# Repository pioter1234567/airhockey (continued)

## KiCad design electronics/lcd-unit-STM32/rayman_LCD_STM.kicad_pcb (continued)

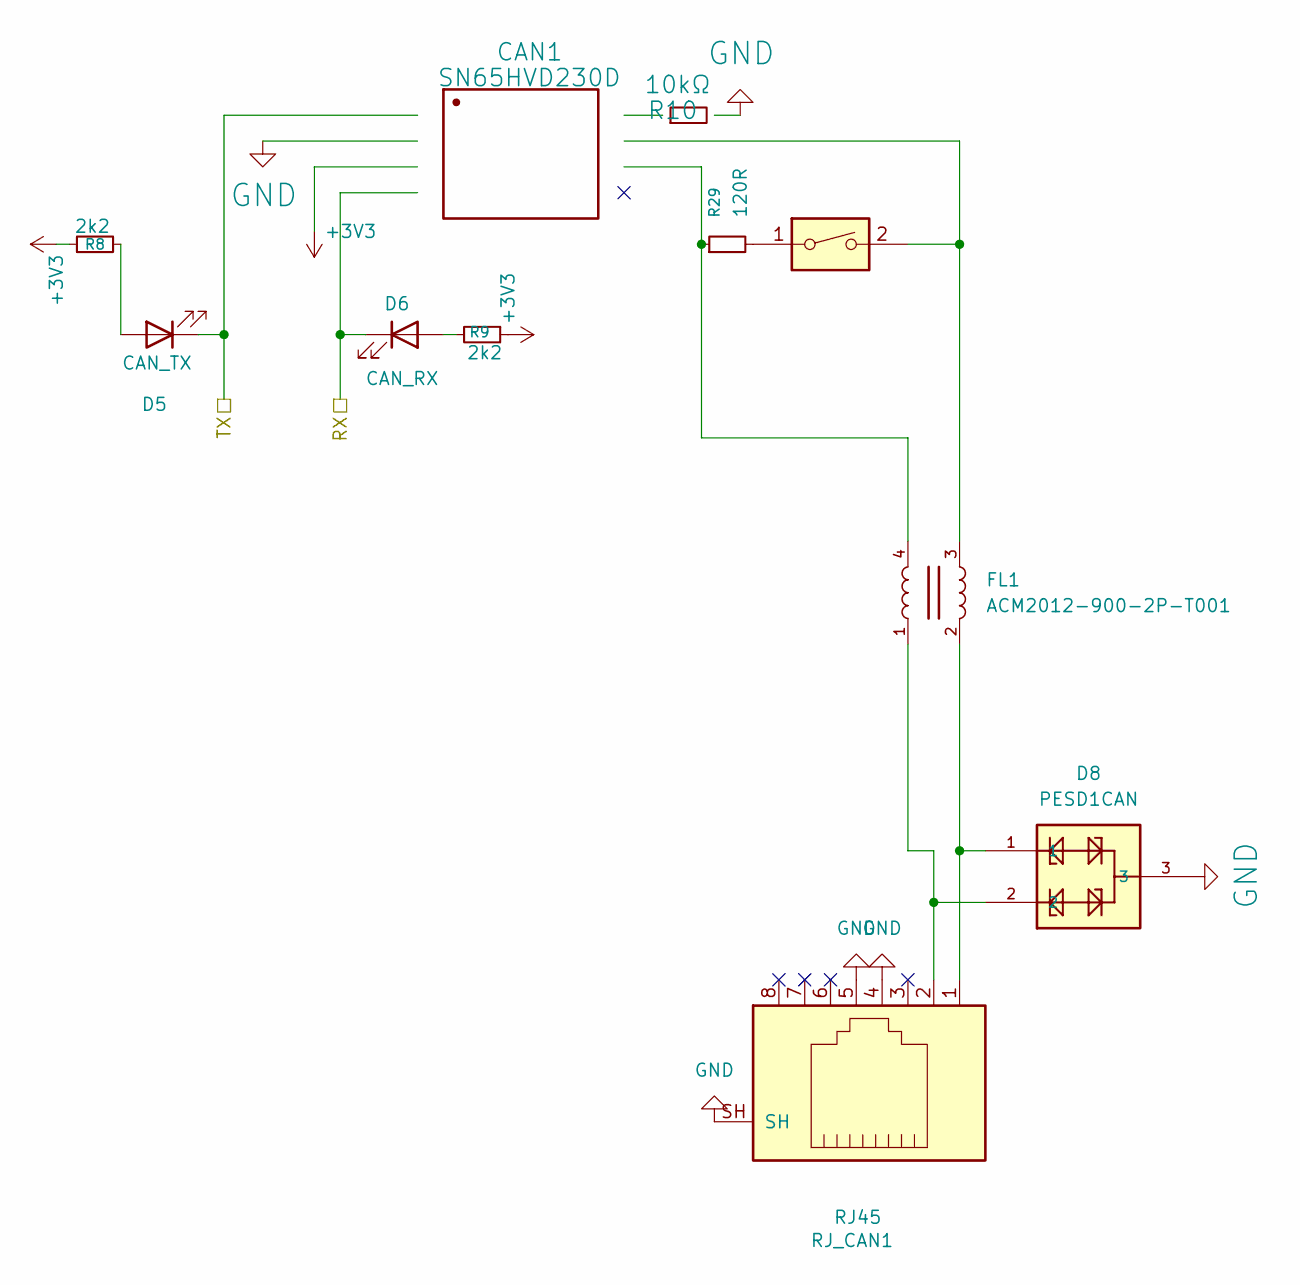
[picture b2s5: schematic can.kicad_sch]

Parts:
CAN1: SN65HVD230D; SOIC127P599X175-8N; Manufacturer Part SN65HVD230D
D5: CAN_TX; LED_0805_2012Metric
D6: CAN_RX; LED_0805_2012Metric
D8: PESD1CAN; SOT23-3
FL1: ACM2012-900-2P-T001; FIL_ACM2012-900-2P-T001
R8, R9: 2k2; R_0805_2012Metric
R10: 10kΩ; R_0805_2012Metric; Manufacturer Part RT0603LRA0710KL
R29: 120R; R_0805_2012Metric
RJ_CAN1: RJ45; RJ45_Amphenol_RJHSE5380
SW_CAN_T1: SW_DIP_x01; SW_DIP_SPSTx01_Slide_6.7x4.1mm_W7.62mm_P2.54mm_LowProfile

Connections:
+3V3: CAN1.3 (VCC), R8.1, R9.1; also elsewhere on the board
GND: CAN1.2 (GND), D8.3, R10.2, RJ_CAN1.4, RJ_CAN1.5, RJ_CAN1.SH; also elsewhere on the board
unnamed: CAN1.7 (CANH), FL1.3, SW_CAN_T1.2
unnamed: CAN1.6 (CANL), FL1.4, R29.1
unnamed: CAN1.8 (RS), R10.1
unnamed: D5.2 (A), R8.2
unnamed: D6.2 (A), R9.2
unnamed: D8.1, FL1.2, RJ_CAN1.1
unnamed: D8.2, FL1.1, RJ_CAN1.2
unnamed: R29.2, SW_CAN_T1.1
pa11: CAN1.4 (R), D6.1 (K); also elsewhere on the board
pa12: CAN1.1 (D), D5.1 (K); also elsewhere on the board

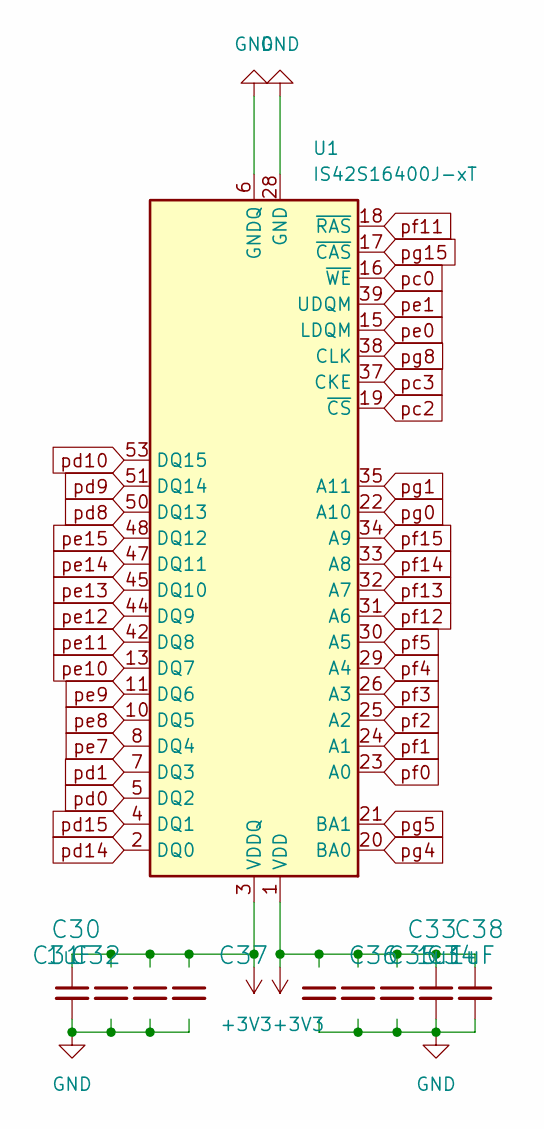
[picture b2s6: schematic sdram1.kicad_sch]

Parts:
C30, C33, C38: 1uF; C_0603_1608Metric; Manufacturer Part 0805ZD106KAT2A
C31, C32, C34, C35, C36, C37: 100nF; C_0603_1608Metric; Manufacturer Part 0805B104K160CT-C
U1: IS42S16400J-xT; TSOP-II-54_22.2x10.16mm_P0.8mm

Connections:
+3V3: C30.1, C31.1, C32.1, C33.1, C34.1, C35.1, C36.1, C37.1, C38.1, U1.1 (VDD), U1.3 (VDDQ), U1.9 (VDDQ), U1.14 (VDD), U1.27 (VDD), U1.43 (VDDQ), U1.49 (VDDQ); also elsewhere on the board
GND: C30.2, C31.2, C32.2, C33.2, C34.2, C35.2, C36.2, C37.2, C38.2, U1.6 (GNDQ), U1.12 (GNDQ), U1.28 (GND), U1.41 (GND), U1.46 (GNDQ), U1.52 (GNDQ), U1.54 (GND); also elsewhere on the board
pc0: U1.16 (~WE); also elsewhere on the board
pc2: U1.19 (~CS); also elsewhere on the board
pc3: U1.37 (CKE); also elsewhere on the board
pd0: U1.5 (DQ2); also elsewhere on the board
pd1: U1.7 (DQ3); also elsewhere on the board
pd8: U1.50 (DQ13); also elsewhere on the board
pd9: U1.51 (DQ14); also elsewhere on the board
pd10: U1.53 (DQ15); also elsewhere on the board
pd14: U1.2 (DQ0); also elsewhere on the board
pd15: U1.4 (DQ1); also elsewhere on the board
pe0: U1.15 (LDQM); also elsewhere on the board
pe1: U1.39 (UDQM); also elsewhere on the board
pe7: U1.8 (DQ4); also elsewhere on the board
pe8: U1.10 (DQ5); also elsewhere on the board
pe9: U1.11 (DQ6); also elsewhere on the board
pe10: U1.13 (DQ7); also elsewhere on the board
pe11: U1.42 (DQ8); also elsewhere on the board
pe12: U1.44 (DQ9); also elsewhere on the board
pe13: U1.45 (DQ10); also elsewhere on the board
pe14: U1.47 (DQ11); also elsewhere on the board
pe15: U1.48 (DQ12); also elsewhere on the board
pf0: U1.23 (A0); also elsewhere on the board
pf1: U1.24 (A1); also elsewhere on the board
pf2: U1.25 (A2); also elsewhere on the board
pf3: U1.26 (A3); also elsewhere on the board
pf4: U1.29 (A4); also elsewhere on the board
pf5: U1.30 (A5); also elsewhere on the board
pf11: U1.18 (~RAS); also elsewhere on the board
pf12: U1.31 (A6); also elsewhere on the board
pf13: U1.32 (A7); also elsewhere on the board
pf14: U1.33 (A8); also elsewhere on the board
pf15: U1.34 (A9); also elsewhere on the board
pg0: U1.22 (A10); also elsewhere on the board
pg1: U1.35 (A11); also elsewhere on the board
pg4: U1.20 (BA0); also elsewhere on the board
pg5: U1.21 (BA1); also elsewhere on the board
pg8: U1.38 (CLK); also elsewhere on the board
pg15: U1.17 (~CAS); also elsewhere on the board

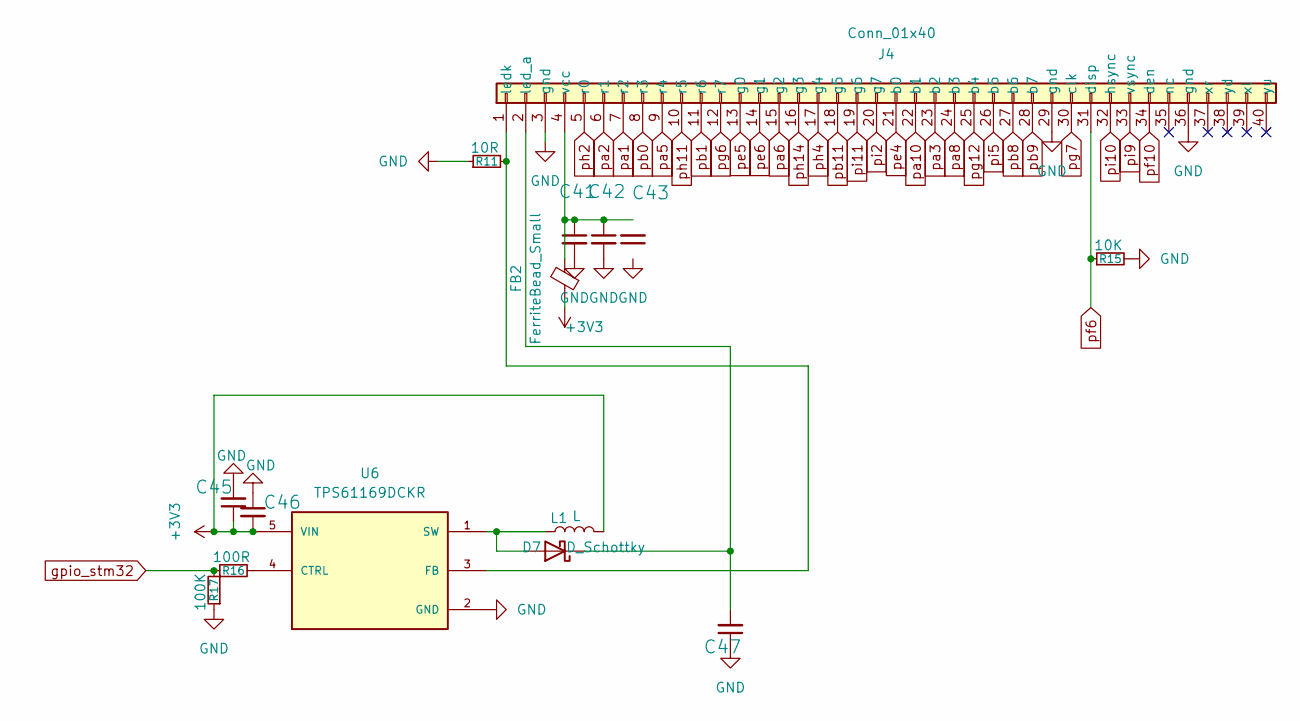
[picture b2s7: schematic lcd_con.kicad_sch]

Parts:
C41: 10uF; C_0603_1608Metric; Manufacturer Part 0805ZD106KAT2A
C42: 1uF; C_0603_1608Metric; Manufacturer Part 0805ZD106KAT2A
C43: 100nF; C_0603_1608Metric; Manufacturer Part 0805B104K160CT-C
C45: 4U7; C_0603_1608Metric; Manufacturer Part 0805B104K160CT-C
C46: 100n; C_0603_1608Metric; Manufacturer Part 0805ZD106KAT2A
C47: 2.2u 50v; C_0603_1608Metric; Manufacturer Part 0805ZD106KAT2A
D7: D_Schottky; D_SMA
FB2: FerriteBead_Small; ferrit_0805
J4: Conn_01x40; TE_4-1734839-0_1x40-1MP_P0.5mm_Horizontal
L1: L; L_Bourns-SRN4018
R11: 10R; R_0805_2012Metric
R15: 10K; R_0805_2012Metric
R16: 100R; R_0805_2012Metric
R17: 100K; R_0805_2012Metric
U6: TPS61169DCKR; SOT65P210X110-5N; PARTREV A

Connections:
+3V3: C45.1, C46.2, FB2.1, L1.2, U6.5 (VIN); also elsewhere on the board
GND: C41.2, C42.2, C43.1, C45.2, C46.1, C47.1, J4.3 (gnd), J4.29 (gnd), J4.36 (gnd), R11.1, R15.2, R17.1, U6.2 (GND); also elsewhere on the board
unnamed: D7.2 (A), L1.1, U6.1 (SW)
unnamed: C47.2, D7.1 (K), J4.2 (led_a)
unnamed: J4.1 (ledk), R11.2, U6.3 (FB)
unnamed: C41.1, C42.1, C43.2, FB2.2, J4.4 (vcc)
unnamed: R16.2, U6.4 (CTRL)
gpio_stm32: R16.1, R17.2; also elsewhere on the board
pa1: J4.7 (r2); also elsewhere on the board
pa2: J4.6 (r1); also elsewhere on the board
pa3: J4.23 (b2); also elsewhere on the board
pa5: J4.9 (r4); also elsewhere on the board
pa6: J4.15 (g2); also elsewhere on the board
pa8: J4.24 (b3); also elsewhere on the board
pa10: J4.22 (b1); also elsewhere on the board
pb0: J4.8 (r3); also elsewhere on the board
pb1: J4.11 (r6); also elsewhere on the board
pb8: J4.27 (b6); also elsewhere on the board
pb9: J4.28 (b7); also elsewhere on the board
pb11: J4.18 (g5); also elsewhere on the board
pe4: J4.21 (b0); also elsewhere on the board
pe5: J4.13 (g0); also elsewhere on the board
pe6: J4.14 (g1); also elsewhere on the board
pf6: J4.31 (disp), R15.1
pf10: J4.34 (den); also elsewhere on the board
pg6: J4.12 (r7); also elsewhere on the board
pg7: J4.30 (clk); also elsewhere on the board
pg12: J4.25 (b4); also elsewhere on the board
ph2: J4.5 (r0); also elsewhere on the board
ph4: J4.17 (g4); also elsewhere on the board
ph11: J4.10 (r5); also elsewhere on the board
ph14: J4.16 (g3); also elsewhere on the board
pi2: J4.20 (g7); also elsewhere on the board
pi5: J4.26 (b5); also elsewhere on the board
pi9: J4.33 (vsync); also elsewhere on the board
pi10: J4.32 (hsync); also elsewhere on the board
pi11: J4.19 (g6); also elsewhere on the board

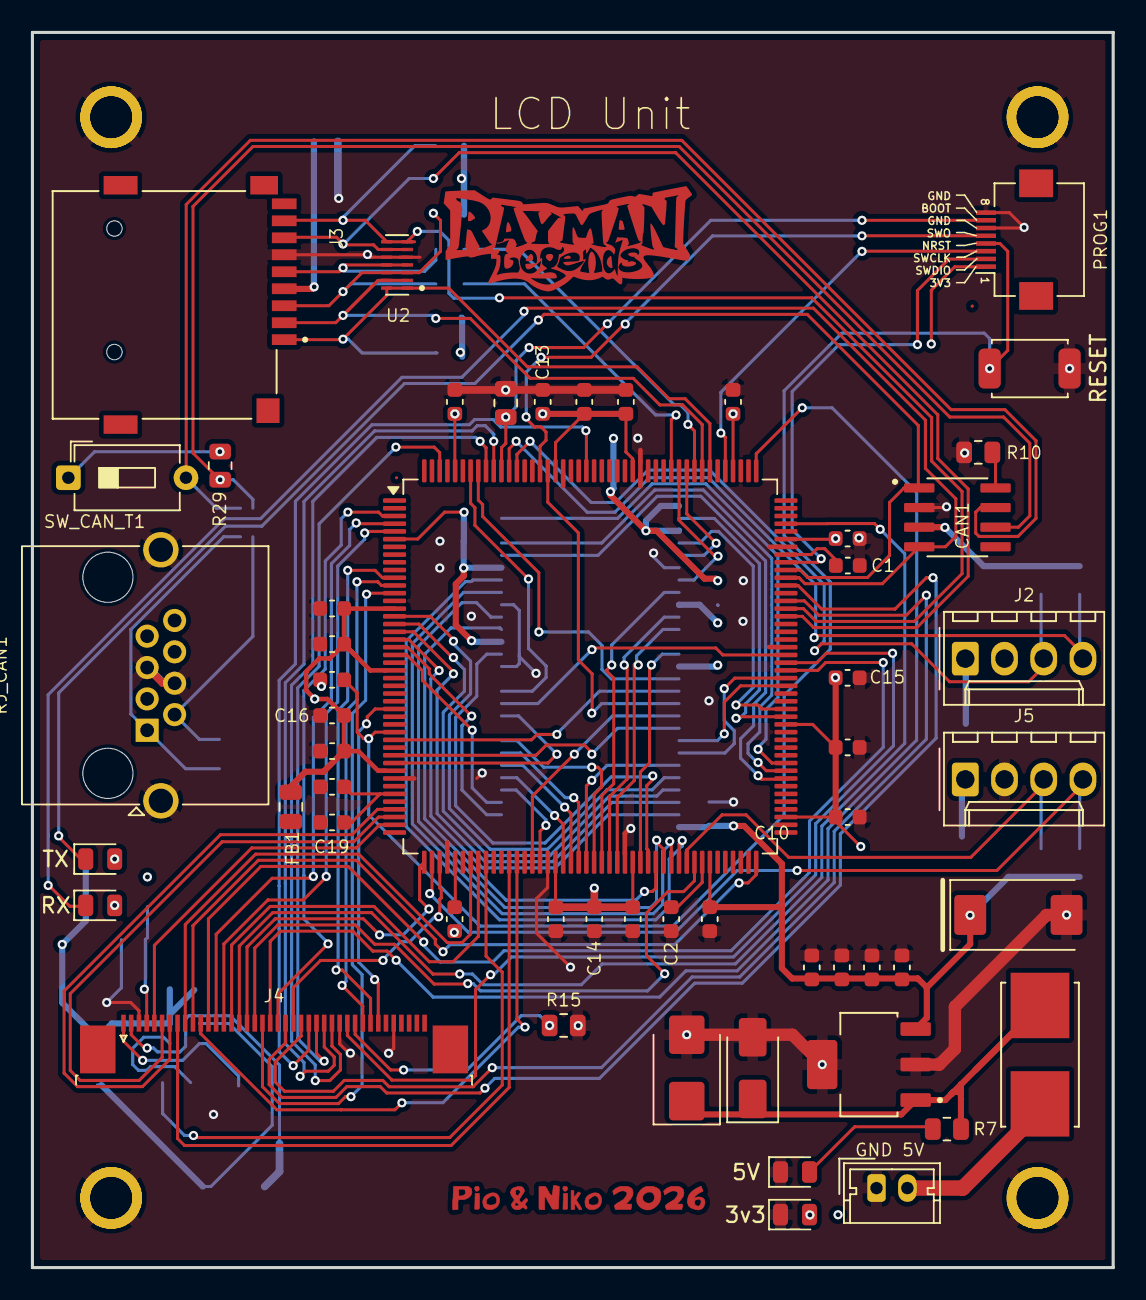
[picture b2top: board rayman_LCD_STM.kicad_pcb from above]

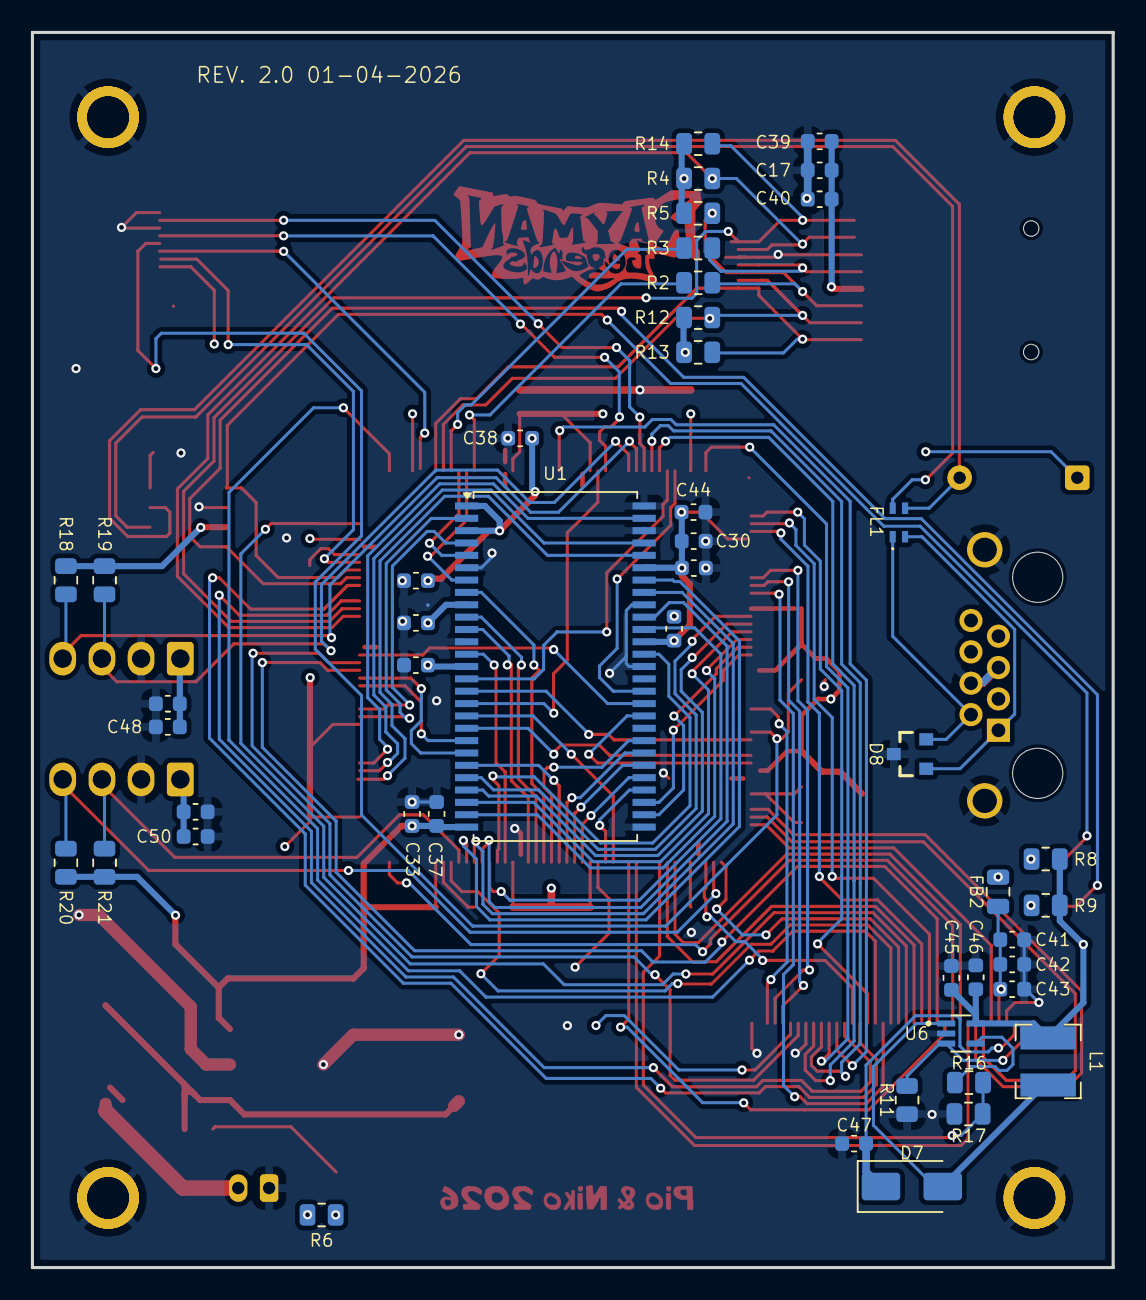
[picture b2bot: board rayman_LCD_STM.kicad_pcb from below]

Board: 4 copper layers, 70.0 x 80.0 mm, 101 parts (47 on the bottom side), 109 nets.

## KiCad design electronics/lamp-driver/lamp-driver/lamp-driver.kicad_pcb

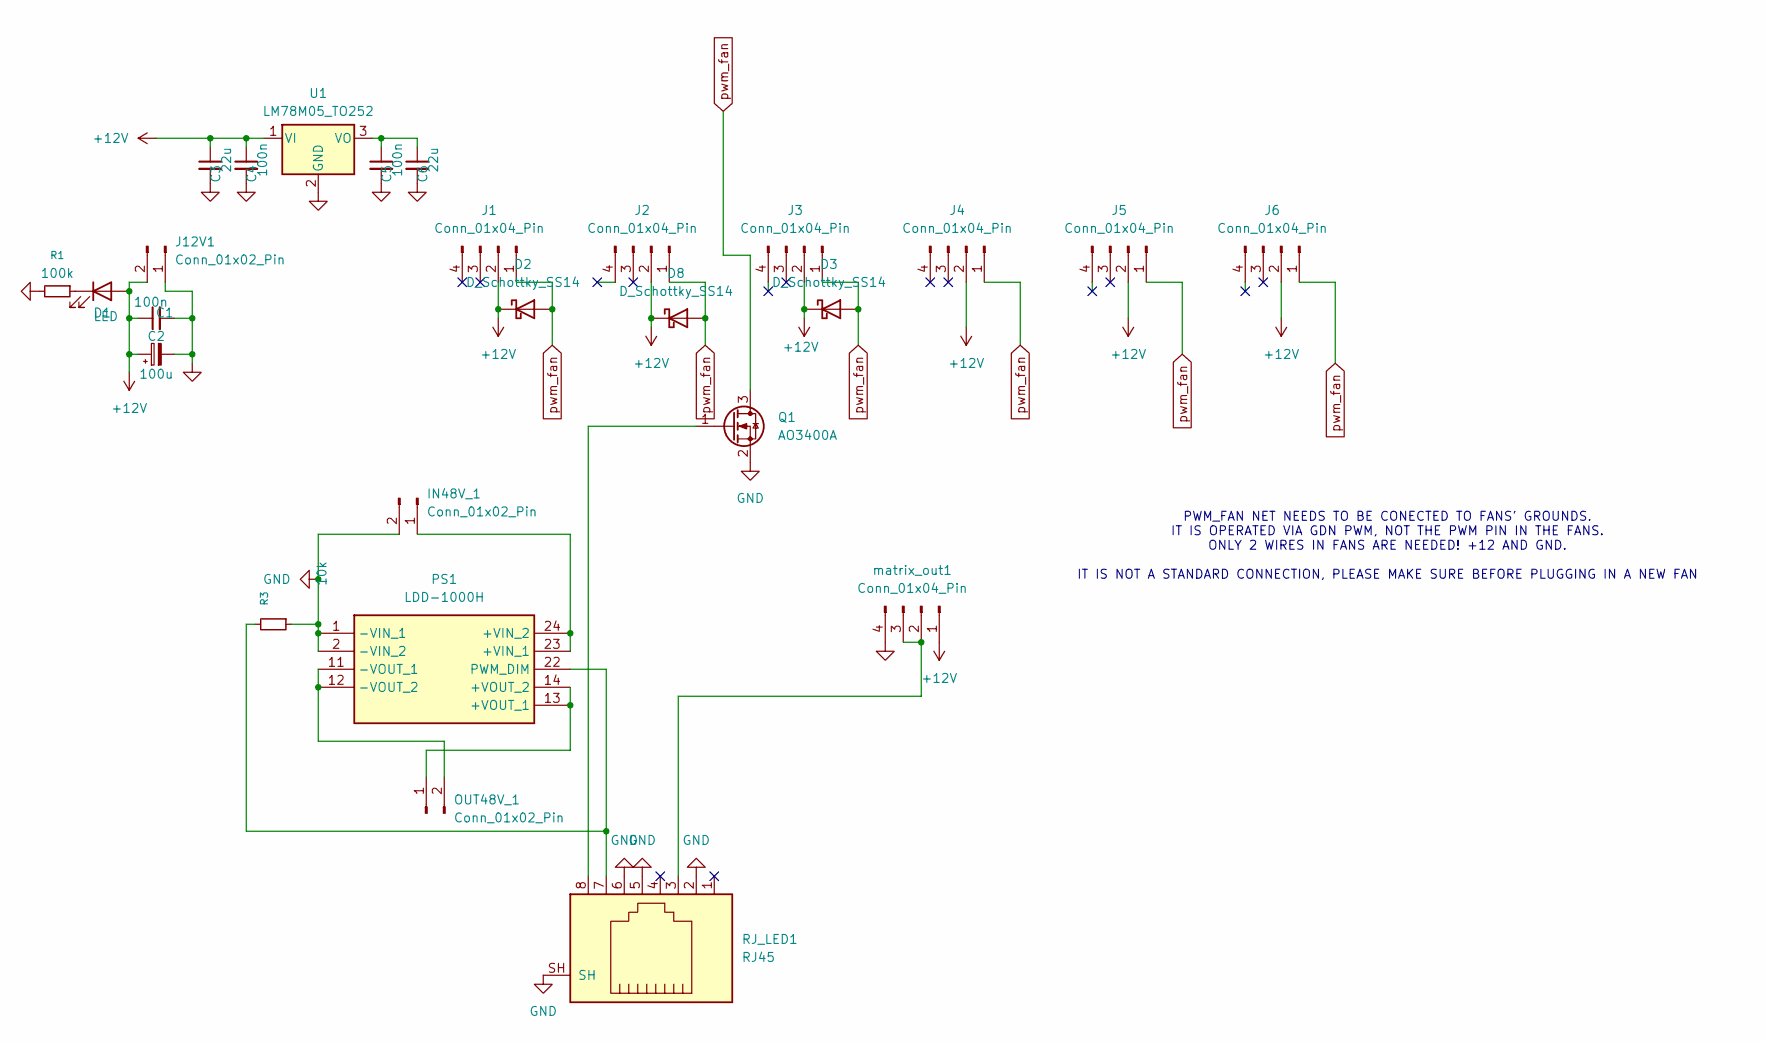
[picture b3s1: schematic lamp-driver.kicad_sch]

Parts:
C1, C4, C5: 100n; C_0805_2012Metric
C2: 100u; CP_Elec_6.3x7.7
C3, C6: 22u; C_0805_2012Metric
D1: LED; LED_0805_2012Metric
D2, D3, D8: D_Schottky_SS14; D_SMA
IN48V_1: Conn_01x02_Pin; Molex_KK-254_AE-6410-02A_1x02_P2.54mm_Vertical
J1, J2, J3, J4, J5, J6: Conn_01x04_Pin; TerminalBlock_Phoenix_MPT-0,5-4-2.54_1x04_P2.54mm_Horizontal
J12V1: Conn_01x02_Pin; Molex_KK-254_AE-6410-02A_1x02_P2.54mm_Vertical
OUT48V_1: Conn_01x02_Pin; Molex_KK-254_AE-6410-02A_1x02_P2.54mm_Vertical
PS1: LDD-1000H; LDD-700H; Mouser Part Number 709-LDD-1000H
Q1: AO3400A; SOT-23
R1: 100k; R_0805_2012Metric
R3: 10k; R_0805_2012Metric
RJ_LED1: RJ45; RJ45_Amphenol_RJHSE5380
U1: LM78M05_TO252; TO-252-2
matrix_out1: Conn_01x04_Pin; TerminalBlock_Phoenix_MPT-0,5-4-2.54_1x04_P2.54mm_Horizontal

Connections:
+12V: C1.1, C2.1, C3.1, C4.1, D1.2 (A), D2.1 (K), D3.1 (K), D8.1 (K), J1.2, J2.2, J3.2, J4.2, J5.2, J6.2, J12V1.2, U1.1 (VI), matrix_out1.1
GND: C1.2, C2.2, C3.2, C4.2, C5.2, C6.2, IN48V_1.2, J12V1.1, PS1.1 (-VIN_1), PS1.2 (-VIN_2), Q1.2 (S), R1.2, R3.1, RJ_LED1.2, RJ_LED1.5, RJ_LED1.6, RJ_LED1.SH, U1.2 (GND), matrix_out1.4
unnamed: D1.1 (K), R1.1
unnamed: IN48V_1.1, PS1.23 (+VIN_1), PS1.24 (+VIN_2)
unnamed: OUT48V_1.1, PS1.13 (+VOUT_1), PS1.14 (+VOUT_2)
unnamed: OUT48V_1.2, PS1.11 (-VOUT_1), PS1.12 (-VOUT_2)
unnamed: PS1.22 (PWM_DIM), R3.2, RJ_LED1.7
unnamed 7: Q1.1 (G), RJ_LED1.8; also elsewhere on the board
unnamed: C5.1, C6.1, U1.3 (VO)
unnamed: RJ_LED1.3, matrix_out1.2, matrix_out1.3
pwm_fan: D2.2 (A), D3.2 (A), D8.2 (A), J1.1, J2.1, J3.1, J4.1, J5.1, J6.1, Q1.3 (D)

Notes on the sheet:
PWM_FAN NET NEEDS TO BE CONECTED TO FANS' GROUNDS. IT IS OPERATED VIA GDN PWM, NOT THE PWM PIN IN THE FANS. ONLY 2 WIRES IN FANS ARE NEEDED! +12 AND GND. IT IS NOT A STANDARD CONNECTION, PLEASE MAKE SURE BEFORE PLUGGING IN A NEW FAN

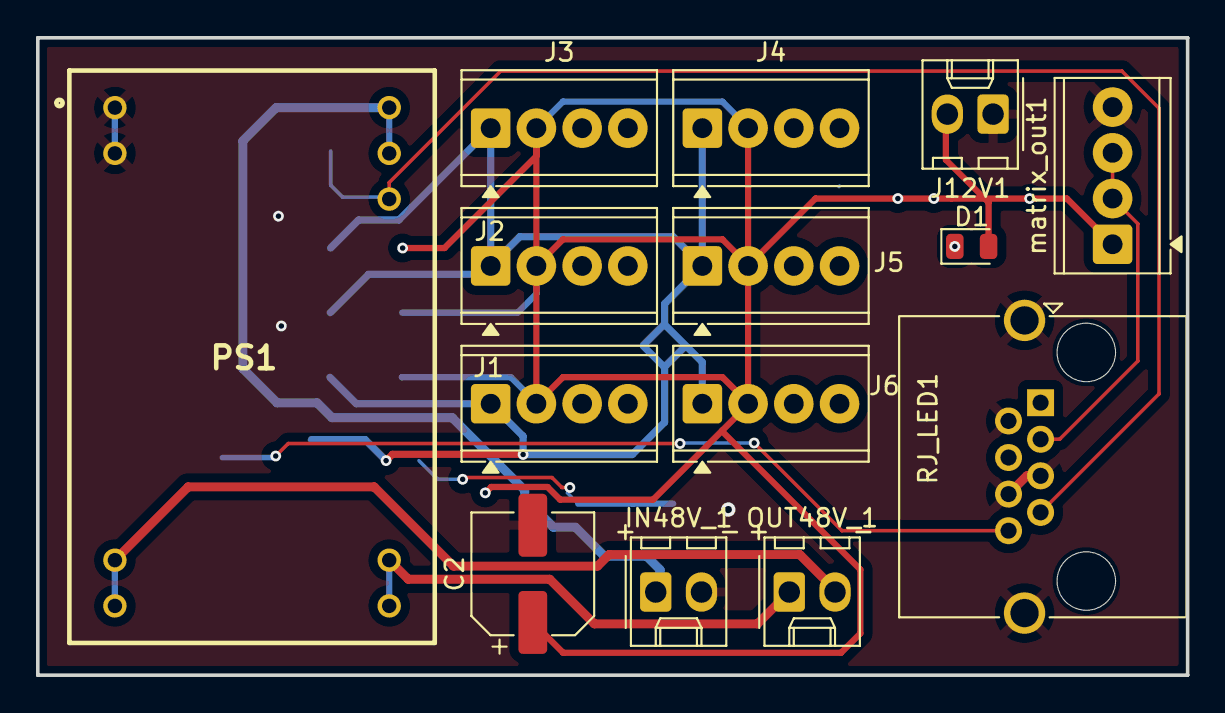
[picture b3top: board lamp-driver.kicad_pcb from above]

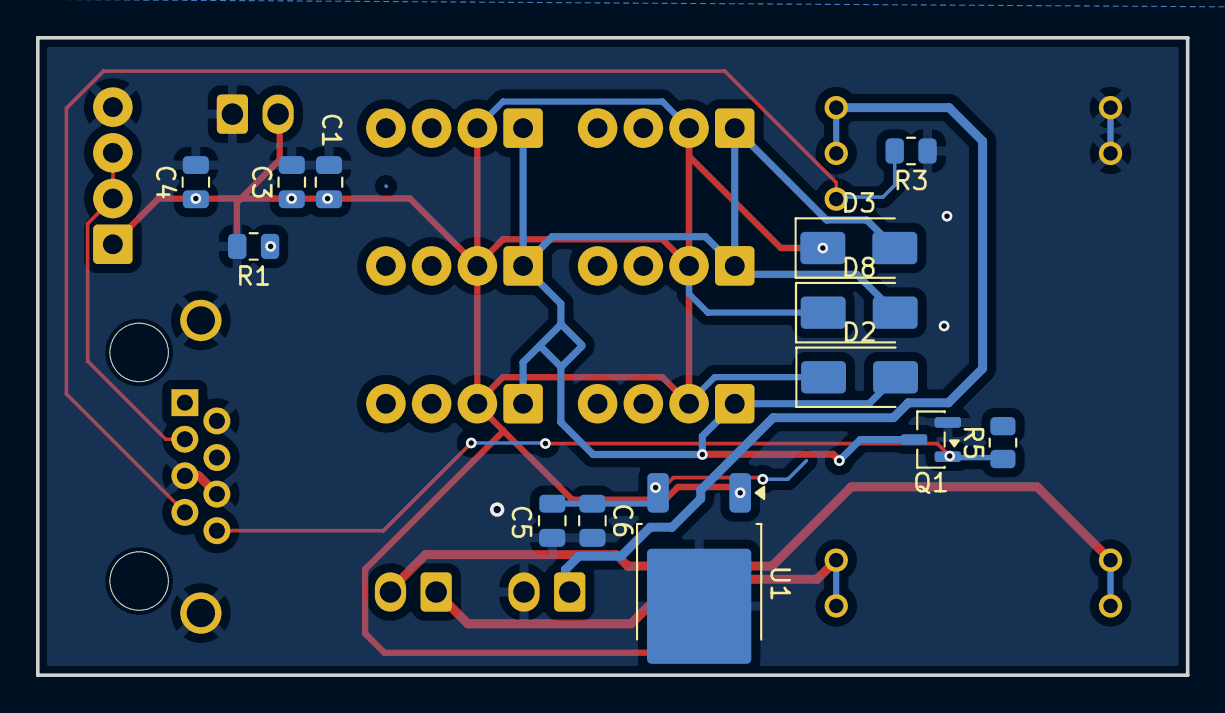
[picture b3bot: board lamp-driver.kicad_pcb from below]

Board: 2 copper layers, 63.9 x 35.4 mm, 27 parts (13 on the bottom side), 11 nets.

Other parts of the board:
R5: 10K; R_0805_2012Metric

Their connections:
unnamed 7: R5.1; also elsewhere on the board

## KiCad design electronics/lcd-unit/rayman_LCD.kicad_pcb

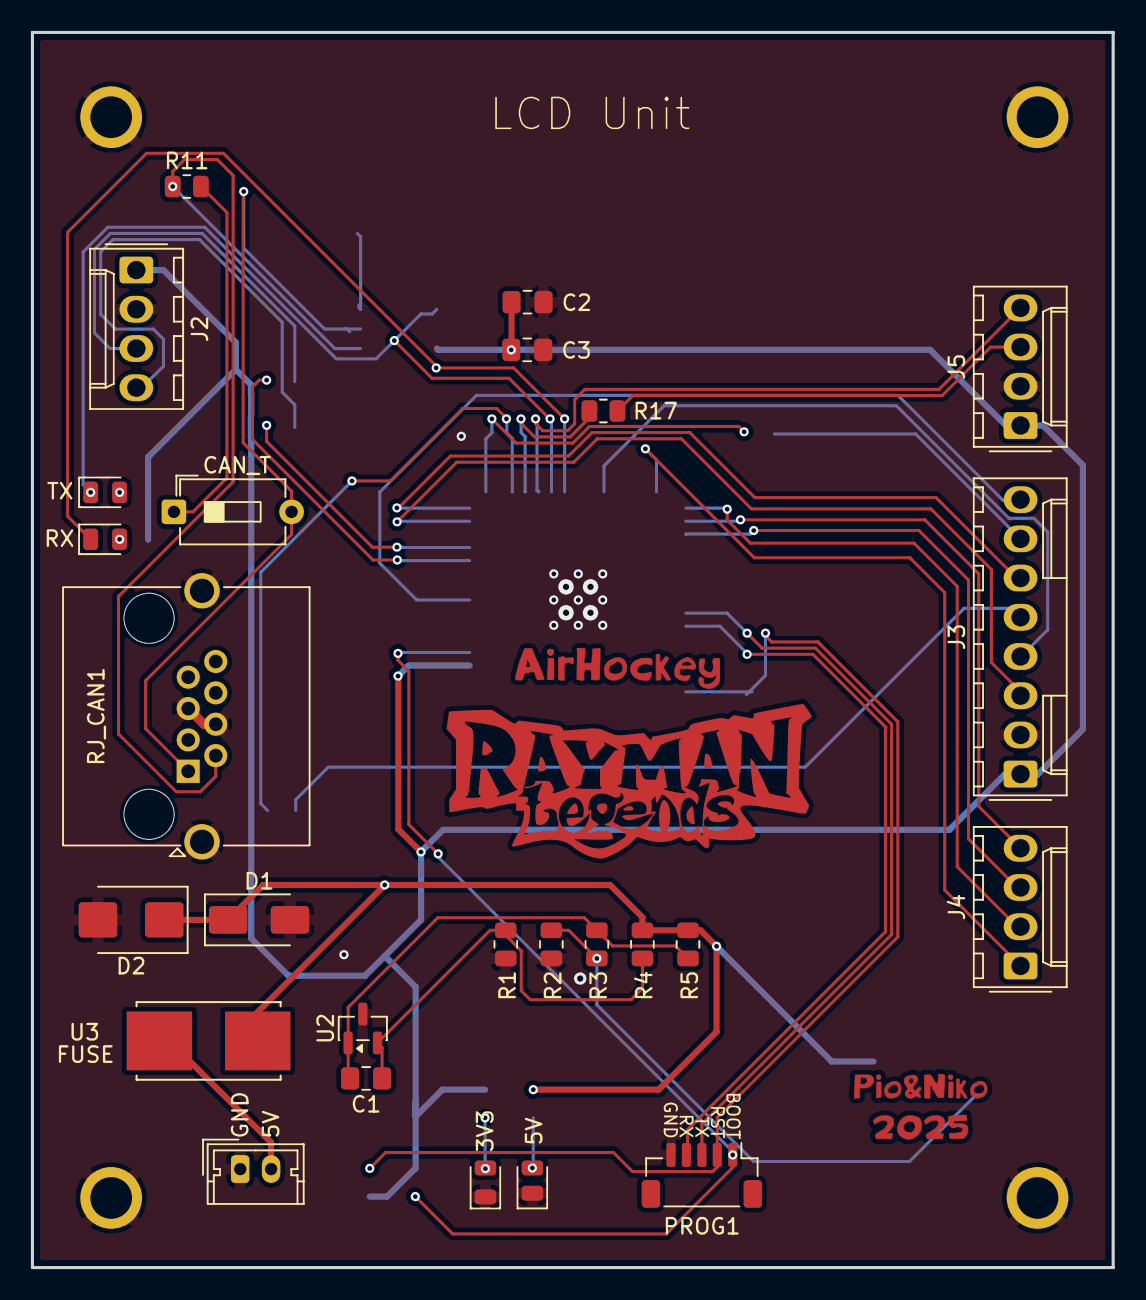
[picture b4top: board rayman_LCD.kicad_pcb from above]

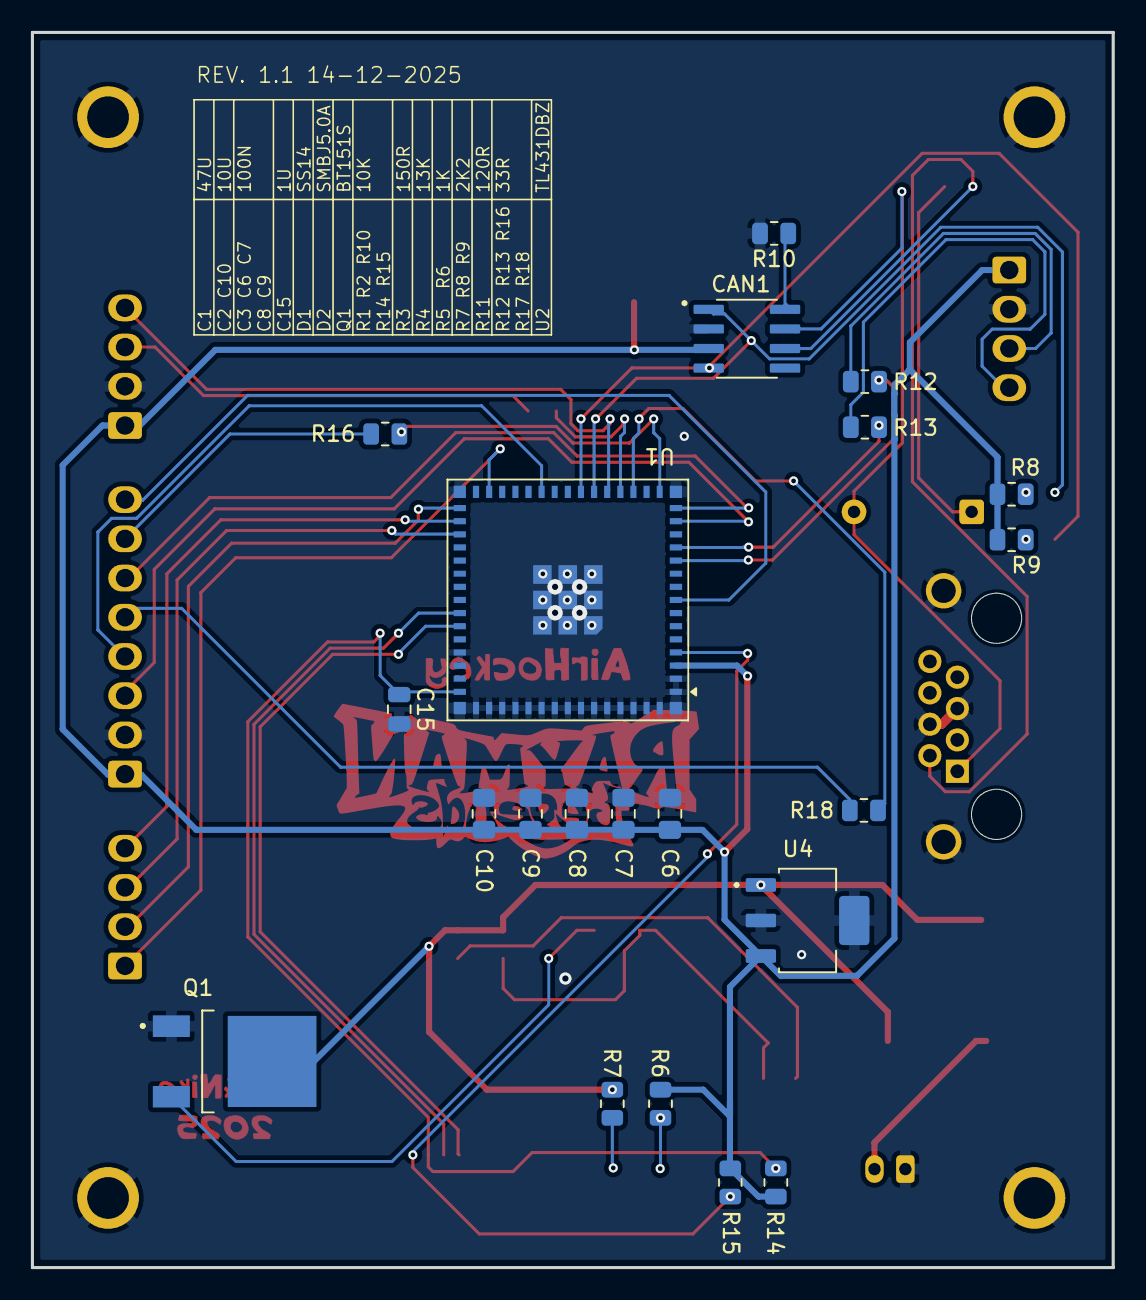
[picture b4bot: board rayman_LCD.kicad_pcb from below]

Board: 2 copper layers, 70.0 x 80.0 mm, 47 parts (21 on the bottom side), 40 nets.

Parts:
C1: 47uF; C_0805_2012Metric_Pad1.18x1.45mm_HandSolder
C2, C10: 10uF; C_0805_2012Metric_Pad1.18x1.45mm_HandSolder
C3, C6, C7, C8, C9: 100nF; C_0805_2012Metric_Pad1.18x1.45mm_HandSolder
C15: 1u; C_0805_2012Metric
CAN1: SN65HVD230D; SOIC127P599X175-8N
D1: D_Schottky; D_SMA
D2: SMBJ5.0A-M3/5B; D_SMB
D3: LED3v3; LED_0805_2012Metric
D4: led5v; LED_0805_2012Metric
D5: CAN_TX; LED_0805_2012Metric
D6: CAN_RX; LED_0805_2012Metric
J1: Conn_01x02_Pin; Molex_Micro-Latch_53253-0270_1x02_P2.00mm_Vertical
J2, J4, J5: Conn_01x04_Pin; Molex_KK-254_AE-6410-04A_1x04_P2.54mm_Vertical
J3: Conn_01x08_Pin; Molex_KK-254_AE-6410-08A_1x08_P2.54mm_Vertical
PROG1: Conn_01x05_Pin; JST_SH_BM05B-SRSS-TB_1x05-1MP_P1.00mm_Vertical
Q1: BT151S-650R; IC_BT136S-600E_118
R1, R2, R10, R14, R15: 10kΩ; R_0805_2012Metric
R3: 150R; R_0805_2012Metric
R4: 13kΩ; R_0805_2012Metric
R5: 1kΩ; R_0805_2012Metric
R6: 1k; R_0805_2012Metric
R7, R8, R9: 2k2; R_0805_2012Metric
R11: 120Ω; R_0805_2012Metric
R12, R13, R16, R17, R18: 33R; R_0805_2012Metric
RJ_CAN1: RJ45; RJ45_Amphenol_RJHSE5380
SW1: SW_DIP_x01; SW_DIP_SPSTx01_Slide_6.7x4.1mm_W7.62mm_P2.54mm_LowProfile
U1: ESP32-S3-MINI-1U; ESP32-S2-MINI-1U
U2: TL431DBZ; SOT-23
U3: 1808 SMD FUSEHOLDER; FUSE_1808
U4: MCP1826S-3302E/DB; MCP1826S-5002EDB

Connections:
+3V3: C2.1, C3.1, C6.1, C7.1, C8.1, C9.1, C10.1, CAN1.3 (VCC), J2.1 (VCC), J3.1 (vdd), J5.1 (VCC), R6.2, R8.1, R9.1, R14.1, R15.2, U1.3 (3V3), U4.3 (VOUT)
+5V: D1.1 (K), D2.1 (K), Q1.2 (A), R4.2, R5.2, R7.1, U3.1, U4.1 (VIN)
/CAN/RX: CAN1.4 (R), D6.1 (K), U1.22 (IO18)
/CAN/TX: CAN1.1 (D), D5.1 (K), U1.21 (IO17)
/Power/+5VDC: J1.2, U3.2
GND: C2.2, C3.2, C6.2, C7.2, C8.2, C9.2, C10.2, C15.2, CAN1.2 (GND), D1.2 (A), D2.2 (A), D3.1 (K), D4.1 (K), J1.1, J2.2 (GND), J3.2 (gnd), J5.2 (GND), PROG1.5, Q1.1 (K), R1.1, R2.1, R10.2, RJ_CAN1.4, RJ_CAN1.5, RJ_CAN1.SH, U1.1 (GND), U1.2 (GND), U1.42 (GND), U1.43 (GND), U1.46 (GND), U1.47 (GND), U1.48 (GND), U1.49 (GND), U1.50 (GND), U1.51 (GND), U1.52 (GND), U1.53 (GND), U1.54 (GND), U1.55 (GND), U1.56 (GND), U1.57 (GND), U1.58 (GND), U1.59 (GND), U1.60 (GND), U1.61 (GND), U1.62 (GND), U1.63 (GND), U1.64 (GND), U1.65 (GND), U2.3 (A), U4.2 (GND), U4.4 (GND)
unnamed: CAN1.7 (CANH), RJ_CAN1.1, SW1.2
unnamed: CAN1.6 (CANL), R11.1, RJ_CAN1.2
unnamed: CAN1.8 (RS), R10.1
unnamed: D3.2 (A), R6.1
unnamed: D4.2 (A), R7.2
unnamed: D5.2 (A), R8.2
unnamed: D6.2 (A), R9.2
unnamed: J2.3 (SCK), R12.1
unnamed: J2.4 (SDK), R13.1
unnamed: J3.8 (bl), U1.8 (IO4)
unnamed: J3.3 (cs), U1.14 (IO10)
unnamed: J3.5 (d/c), R18.1
unnamed: J3.4 (rst), U1.25 (IO21)
unnamed: J3.7 (sck), R16.1
unnamed: J3.6 (sdi), U1.15 (IO11)
unnamed: J4.4 (clk), U1.32 (IO36)
unnamed: J4.1 (scs), U1.29 (IO34)
unnamed: J4.2 (sdi), U1.31 (IO35)
unnamed: J4.3 (sdo), U1.33 (IO37)
unnamed: J5.3 (SCK), R17.1
unnamed: J5.4 (SDK), U1.20 (IO16)
unnamed: Q1.3 (G), R2.2, R3.1
unnamed: R11.2, SW1.1
unnamed: R12.2, U1.11 (IO7)
unnamed: R13.2, U1.12 (IO8)
unnamed: R16.2, U1.16 (IO12)
unnamed: R18.2, U1.18 (IO14)
unnamed: R17.2, U1.19 (IO15)
unnamed: C1.2, R3.2, R5.1, U2.1 (K)
unnamed: C1.1, R1.2, R4.1, U2.2 (REF)
en: C15.1, PROG1.2, R14.2, U1.45 (EN)
io0: PROG1.1, R15.1, U1.4 (IO0)
rxd0: PROG1.4, U1.40 (RXD0)
txd0: PROG1.3, U1.39 (TXD0)
